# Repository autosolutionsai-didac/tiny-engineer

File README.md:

# Vibe Bot

> Give your AI coding agents a body.

> **Based on [Tiny Engineer](https://github.com/jamro/tiny-engineer) by Krzysztof Jamroz** (github.com/jamro/tiny-engineer). Vibe Bot is an independent fork: XIAO ESP32S3 port, multi-session LED bar, and the `vibebot-hub` session aggregator. It is not an official Tiny Engineer product and is not endorsed by the upstream author. Upstream copyright and licence notices are kept — see [License](#license).

> **Photos:** fork-specific photos and a demo of Vibe Bot are TBD. The upstream preview images in `docs/` depict Tiny Engineer branding and are kept only for attribution history; they are not this product's branding (see [TRADEMARK.md](TRADEMARK.md)). For the original robot in action, see the [upstream Tiny Engineer demo video](https://youtu.be/RX_QRxdXMjg).

Vibe Bot is an open-source, 3D-printable desktop robot that physically acts out what your AI coding agents are doing: reading, thinking, coding, finishing tasks (with an audio cue). It runs on an ESP32 over Wi-Fi and exposes a simple REST API, so any tool that can make an HTTP request can drive it.

**[Build your own](#build-your-own) · [How it works](#how-it-works) · [API](docs/api.md) · [Sessions](docs/sessions.md)**

## Why?

AI coding agents increasingly spend long stretches working on their own. Instead of another spinner or status line, Vibe Bot is a tiny teammate on your desk that visibly reads, thinks, and types while the agents work — and its LED bar shows every running session at a glance.

## How it works

```mermaid
flowchart LR
  Agent[AI agent working] --> Integration[Integration sends events]
  Integration -->|HTTP over Wi-Fi| API[Vibe Bot REST API]
  API --> Robot[Robot moves and reacts]
```

An AI agent works; an integration turns that into events; the robot’s REST API on your LAN receives them; the hardware moves and reacts.

**How it connects**

- **Cursor** — Cursor Agent → Cursor hooks → `vibebot-cursor` script → HTTP over Wi-Fi
- **Antigravity CLI** — Antigravity Agent → lifecycle hooks → `vibebot-antigravity` script → HTTP over Wi-Fi
- **Claude Code** — Claude Code → project hooks → `vibebot-claude-code` script → HTTP over Wi-Fi
- **Bring your own** — Codex or any other agent → your script/plugin/app → HTTP REST

All hit the same Vibe Bot REST API (`/anim`, or `/session` for multi-session state). The ESP32 (Seeed XIAO ESP32S3; legacy ESP32-C3-Zero) runs that API, robot logic, and animations, then drives (and plays audio):

| Hardware | Role |
| --- | --- |
| PCA9685 → 5× servos | Head / neck, hands / body |
| Waveshare 0.91inch OLED (SSD1306) | Status, face, info |
| MAX98357A → speaker | Audio |
| 74AHCT1G125 → 9× WS2812B (XIAO build) | Lamp LED + 8-LED session bar |

Cursor is one example client, not the architecture. Details: [Cursor hooks](docs/hooks.md) · [any integration](docs/integration.md) · [HTTP API](docs/api.md)

## Build your own

**Start here:** [docs/getting-started.md](docs/getting-started.md) — thin checklist (shop → print → wire → flash → assemble → wizard → prove → agent).

New to hardware? Optional skim of **[From Code to Circuits](docs/hardware-for-software-engineers/README.md)** — then return to the checklist.

## Hardware overview

Major pieces (exact models and counts in the BOM):

| Role | Part | Qty |
| --- | --- | --- |
| Main Controller | [Seeed Studio XIAO ESP32S3](https://www.seeedstudio.com/XIAO-ESP32S3-p-5627.html) (legacy build: [Waveshare ESP32-C3-Zero](https://www.waveshare.com/esp32-c3-zero.htm), `pio run -e esp32-c3-devkitm-1`) | 1 |
| Servo Controller PWM | [Adafruit PCA9685](https://www.adafruit.com/product/815) | 1 |
| Actuators | Analog micro servos — **Tower Pro SG90 recommended**; Feetech FS0307 for a compact build; Parametrically designed for any standard micro servos | 5 |
| Display | [Waveshare 0.91inch OLED Module](https://www.waveshare.com/0.91inch-oled-module.htm) (SSD1306, 128×32, I2C) | 1 |
| Audio | [MAX98357A](https://www.adafruit.com/product/3006) + [8 Ω / 1 W speaker](https://www.adafruit.com/product/3923) | 1 + 1 |
| LEDs | 9× WS2812B (1 lamp + 8-LED session bar) via a 74AHCT1G125 level shifter, 330 Ω series resistor | 9 |
| USB / power | Dedicated USB-C power input ([Adafruit 5993 USB-C breakout](https://www.adafruit.com/product/5993) or equivalent), **5 V / 3 A** supply, SS14 Schottky into the XIAO 5V pin, 470 µF bulk capacitor | 1 |
| Structure | 3D-printed parts | — |

Complete inventory and limits: [docs/hardware/components.md](docs/hardware/components.md). What to buy (cart + which servo): [docs/shopping.md](docs/shopping.md).

## Quick start

Firmware is Arduino on [PlatformIO](https://platformio.org/). From the project root:

```bash
pio run                 # build
pio run -t upload       # flash firmware + LittleFS
pio device monitor      # serial (115200)
```

If servos move but audio is silent, run `pio run -t uploadfs` once.

**Wi-Fi (first boot):** join `VibeBot-XXXX`, open `http://192.168.4.1/config`. Wizard: servos, screen orientation, RGB LED, speaker, then a **2.4 GHz** network. OLED shows the join-AP steps.

**Web UI:** `http://vibebot.local/` (or the IP on the OLED) — settings, hardware tests, animations.

**Make it move:**

```bash
curl -X POST "http://vibebot.local/anim?name=ring"
```

Full route list: [docs/api.md](docs/api.md). Settings: [docs/settings.md](docs/settings.md).

## AI integrations

Anything that can `POST` over HTTP can drive the robot:

```bash
curl -X POST "http://vibebot.local/anim?name=typing"
```

Useful `name` values: `typing`, `reading`, `thinking`, `ring`, `welcome`, `wakeup`, `sleep`, `attention`, `error`, `abort`, `dead`, `none`.

**Several agents at once:** report each session with `POST /session?id=…&state=idle|working|waiting|error|ended[&activity=typing|reading|thinking][&agent=…][&label=…]` (list: `GET /sessions`, reset: `POST /sessions/clear`). The robot picks one animation by priority and shows every session on the LED bar. Sessions come from the `vibebot-hub` REST pusher or an AgentDeck daemon on the LAN (`agentdeck` setting, default on) — [docs/sessions.md](docs/sessions.md).

Cursor projects can map agent events to poses via hooks — [docs/hooks.md](docs/hooks.md). Broader patterns and examples: [docs/integration.md](docs/integration.md). Optional extra: sleep/wake when you lock or unlock a Mac — [docs/macos-lock-unlock.md](docs/macos-lock-unlock.md).

## Documentation

| Goal | Doc |
| --- | --- |
| Build end-to-end | [docs/getting-started.md](docs/getting-started.md) |
| Flash firmware | [docs/flash.md](docs/flash.md) |
| Parts / cart | [docs/shopping.md](docs/shopping.md) |
| Wiring / power | [docs/hardware/README.md](docs/hardware/README.md) |
| Printable parts | [3d_models/README.md](3d_models/README.md) |
| Assemble printed parts | [docs/3d/assembly.md](docs/3d/assembly.md) |
| Resize CAD for another servo | [docs/3d/parametric-design.md](docs/3d/parametric-design.md) |
| Servo axes / safe ranges | [docs/robot-movement.md](docs/robot-movement.md) |
| HTTP API | [docs/api.md](docs/api.md) |
| Settings | [docs/settings.md](docs/settings.md) |
| Cursor hooks | [docs/hooks.md](docs/hooks.md) |
| Any IDE / REST | [docs/integration.md](docs/integration.md) |
| Firmware / package tests | [docs/testing.md](docs/testing.md) |
| Full index | [docs/README.md](docs/README.md) |

## Build one, break one, share it

Print it, wire it, change the CAD, swap animations, or hook up a different agent. Issues and PRs welcome — especially new integrations. See [CONTRIBUTING.md](CONTRIBUTING.md). Vulnerabilities: [SECURITY.md](SECURITY.md). Conduct: [CODE_OF_CONDUCT.md](CODE_OF_CONDUCT.md).

## License

- **Software** (firmware, integrations, scripts, documentation) — [MIT](LICENSE)
- **Hardware designs** (CAD source and `.3mf` printables in [`3d_models/`](3d_models/); KiCad PCBs in [`hardware/`](hardware/)) — [CERN-OHL-S-2.0](3d_models/LICENSE)

Copyright (c) 2026 Krzysztof Jamroz and contributors. Vibe Bot is based on the Tiny Engineer open hardware design by Krzysztof Jamroz; the upstream Source Location for the CERN-OHL-S designs remains `https://github.com/jamro/tiny-engineer` (see [3d_models/NOTICE](3d_models/NOTICE) and [hardware/NOTICE](hardware/NOTICE)).

See [LICENSING.md](LICENSING.md) for scope and effective date. The **Tiny Engineer** name, logo, AI emblem, and branded project images are not licensed and are not used as this fork's branding — see [TRADEMARK.md](TRADEMARK.md).

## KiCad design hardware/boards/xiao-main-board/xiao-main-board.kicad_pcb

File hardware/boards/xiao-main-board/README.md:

# xiao-main-board

Carrier PCB for the Seeed XIAO ESP32S3 build: hand-solderable sockets for the existing modules, a 5 V / 3 A power input, a buffered WS2812 output, and small aux headers. Same idea as [`main-control-board`](../main-control-board/) (sockets, not integrated chips), sized for the robot base.

- **Status:** draft, not manufactured (rev v0.1, 2026-10-18). Schematic and fully routed layout, KiCad review only.
- **KiCad:** 10 (checked with kicad-cli 10.0.7)
- **Board:** 70.0 × 45.0 mm, 2 layers, FR4 1.6 mm, 1 oz. GND pour on both layers with stitching vias. 4 × M2 mounting holes (2.2 mm NPTH) at (10.7, 3.0), (59.3, 3.0), (10.7, 35.4) and (59.3, 35.4) mm from the top-left corner. The two lower holes sit under the XIAO and the MAX98357A modules, so screw the board down before plugging those in.
- **Interfaces:** XIAO ESP32S3 (2 × 1×7 sockets), Adafruit PCA9685 #815 (2 × 1×6 sockets), MAX98357A breakout (1×7 socket), SSD1306 OLED (1×4 header), Adafruit 5993 USB-C breakout (1×4 socket, power only), 2-pin screw terminal, WS2812 JST-PH 3-pin, touch 1×2 header, UART 1×3 header.
- **Built:** not manufactured. **Tested:** not tested.
- **ERC / DRC:** `python3 scripts/check_pcb.py` passes: ERC 0 errors, DRC 0 errors / 0 unconnected / 0 schematic-parity issues, and the netlist matches `expected-nets.yml`. The remaining warnings are listed under [Known warnings](#known-warnings).

Pin plan and firmware mapping: [`include/pins.h`](../../../include/pins.h) and [`docs/hardware/pinout.md`](../../../docs/hardware/pinout.md). Contribution rules: [`docs/pcb.md`](../../../docs/pcb.md).

## XIAO ESP32S3 pinout used

The XIAO plugs in with its USB-C facing the left board edge. The receptacle overhangs the board by about 1.5 mm, and the overhang is marked on silkscreen and courtyard.

| XIAO | GPIO | Net | Goes to |
| --- | --- | --- | --- |
| D0 | 1 | `LED_DIN_3V3` | U2 74AHCT1G125 input A |
| D1 | 2 | `TOUCH_D1` | J8.1 (reserved: touch pad or button) |
| D2 | 3 | open | S3 strapping pin, left unused |
| D3 | 4 | `PCA_OE` | J1.5 / J2.5 PCA9685 OE (active low) |
| D4 | 5 | `I2C_SDA` | PCA9685, OLED, optional R2 |
| D5 | 6 | `I2C_SCL` | PCA9685, OLED, optional R3 |
| D6 | 43 | `UART_TX` | J9.1 |
| D7 | 44 | `UART_RX` | J9.2 |
| D8 | 7 | `I2S_BCLK` | J3.2 MAX98357A BCLK |
| D9 | 8 | `I2S_LRC` | J3.1 MAX98357A LRC |
| D10 | 9 | `I2S_DIN` | J3.3 MAX98357A DIN |
| 5V | – | `+5V_XIAO` | D1 SS14 cathode |
| 3V3 | – | `+3V3` | PCA9685 VCC, OLED VCC, R2/R3 |
| GND | – | `GND` | |

Source for the pin numbers: Seeed's own KiCad library ([Seeed-Studio/OPL_Kicad_Library](https://github.com/Seeed-Studio/OPL_Kicad_Library), commit `b0035c5`, "Seeed Studio XIAO Series Library": symbol `XIAO-ESP32-S3-SMD` and footprint `XIAO-ESP32-S3-DIP`). Pins 1–7 are D0–D6 down the left side with USB at the top. Pins 8–14 are D7, D8, D9, D10, 3V3, GND and 5V going up the right side. That matches the Seeed wiki pinout (left side D0…D6, right side 5V, GND, 3V3, D10, D9, D8, D7 from top to bottom). The project symbol and footprint (`libraries/`, nickname `XiaoMainBoard`) were redrawn from those dimensions: 21 × 17.8 mm module, 2.54 mm pitch, rows 15.24 mm apart.

## Power

```
J5 (5993 VBUS) ─┐
J6 (terminal +)─┴─ +5V rail ─┬─ C1 470 µF + C2 100 nF
                             ├─ J1.1 / J2.1  PCA9685 V+ (servos)   ← 1.5 mm back-layer trunk
                             ├─ J3.7 MAX98357A VIN
                             ├─ J7.1 LED chain + U2 VCC (C3 100 nF)
                             └─ D1 SS14 ──► +5V_XIAO ── XIAO 5V pin
```

- **SS14 orientation** (confirmed in the `kicad-cli sch export netlist` output): **anode `D1.2:A` on `+5V`** (the rail) and **cathode `D1.1:K` on `+5V_XIAO`**, which is the XIAO 5V pin `U1.14`. The rail can feed the XIAO, but a USB host plugged into the XIAO cannot back-feed the servo rail. The SMA cathode band is pad 1, toward the left (XIAO) side. The silkscreen shows the band.
- Use a single **5 V / 3 A** supply on J5 (Adafruit 5993) **or** J6 (screw terminal), not both at once. The XIAO's own USB-C is for flashing and serial only. Do not power the servos from it.
- PCA9685 **VCC** = `+3V3` (logic) and **V+** = `+5V` (servo rail). They are separate nets. Do not bridge them.
- When the XIAO USB and the rail are both live, the XIAO 5V pin sees about rail − 0.35 V through D1 and the host's VBUS in parallel. A rail above about 5.3 V could make the rail the supply that wins (see [review items](#needs-human-review-before-ordering)).
- Net classes in `xiao-main-board.kicad_pro`, with matching rules in `xiao-main-board.kicad_dru`:

  | Class | Nets | Default width | DRU minimum |
  | --- | --- | --- | --- |
  | `Power5V` | `+5V` | 1.2 mm | 1.0 mm |
  | `Power5VXiao` | `+5V_XIAO` | 0.6 mm | 0.5 mm |
  | `Power3V3` | `+3V3` | 0.4 mm | 0.4 mm |
  | `GND` | `GND` | 0.4 mm | 0.4 mm |
  | `Default` | signals | 0.25 mm | – |

  The servo trunk from J6 through C1 to both PCA9685 V+ pins is 1.5 mm on the back layer.

## Connector pinouts

| Ref | Part | Pin 1 → n |
| --- | --- | --- |
| U1 | XIAO ESP32S3 on 2 × 1×7 sockets | see table above |
| J1, J2 | PCA9685 #815 sockets, 58.42 mm apart | 1 V+ (`+5V`), 2 VCC (`+3V3`), 3 SDA, 4 SCL, 5 OE (`PCA_OE`), 6 GND. Same order as main-control-board; V+ is the lower pin. |
| J3 | MAX98357A 1×7 socket | 1 LRC, 2 BCLK, 3 DIN, 4 GAIN (open), 5 SD (open), 6 GND, 7 VIN (`+5V`) |
| J4 | OLED 1×4 male header | 1 VCC (`+3V3`), 2 GND, 3 SDA, 4 SCL. Same order as main-control-board J2. |
| J5 | Adafruit 5993 1×4 socket | 1 D+ (open), 2 D− (open), 3 VBUS (`+5V`), 4 GND. Same order as main-control-board J7; data is not used. |
| J6 | Screw terminal, 3.5 mm pitch | 1 `+5V`, 2 GND. The wire entry faces the bottom edge. |
| J7 | JST-PH 3-pin (B3B-PH-K) | 1 `+5V`, 2 DATA (`LED_DATA`, after 330 Ω), 3 GND. Chain: index 0 lamp LED, then the 8-LED session bar. |
| J8 | 1×2 header | 1 `TOUCH_D1` (XIAO D1), 2 GND |
| J9 | 1×3 header | 1 TX (D6), 2 RX (D7), 3 GND. These are XIAO-side names: connect the adapter's RX to pin 1. |

## BOM

| Qty | Ref | Value / part | Footprint | Example part number |
| --- | --- | --- | --- | --- |
| 1 | U1 | Seeed Studio XIAO ESP32S3 (U.FL antenna included) | `XiaoMainBoard:Seeed_XIAO_ESP32S3_Socketed` | Seeed 113991114 |
| 2 | (U1) | 1×7 female header, 2.54 mm, 8.5 mm tall | (part of the U1 footprint) | Würth 61300711821 |
| 1 | U2 | 74AHCT1G125, SOT-23-5 | `Package_TO_SOT_SMD:SOT-23-5` | TI SN74AHCT1G125DBVR |
| 1 | D1 | SS14 Schottky, 1 A 40 V | `Diode_SMD:D_SMA` | SS14 (onsemi / MCC) |
| 1 | C1 | 470 µF 10 V electrolytic, 8 × 11.5 mm | `Capacitor_THT:CP_Radial_D8.0mm_P3.50mm` | Panasonic EEU-FR1A471 |
| 2 | C2, C3 | 100 nF X7R 25 V | `Capacitor_SMD:C_0805_2012Metric` | Yageo CC0805KRX7R9BB104 |
| 1 | R1 | 330 Ω 1 % | `Resistor_SMD:R_0805_2012Metric` | Yageo RC0805FR-07330RL |
| 2 | R2, R3 | 4.7 kΩ 1 %, **DNP** | `Resistor_SMD:R_0805_2012Metric` | Yageo RC0805FR-074K7L |
| 2 | J1, J2 | 1×6 female header, 2.54 mm | `Connector_PinSocket_2.54mm:PinSocket_1x06_P2.54mm_Vertical` | Würth 61300611821 |
| 1 | J3 | 1×7 female header, 2.54 mm | `…PinSocket_1x07_P2.54mm_Vertical` | Würth 61300711821 |
| 1 | J5 | 1×4 female header, 2.54 mm | `…PinSocket_1x04_P2.54mm_Vertical` | Würth 61300411821 |
| 1 | J4 | 1×4 male header | `Connector_PinHeader_2.54mm:PinHeader_1x04_P2.54mm_Vertical` | Würth 61300411121 |
| 1 | J9 | 1×3 male header | `…PinHeader_1x03_P2.54mm_Vertical` | Würth 61300311121 |
| 1 | J8 | 1×2 male header | `…PinHeader_1x02_P2.54mm_Vertical` | Würth 61300211121 |
| 1 | J6 | 2-pin screw terminal, 3.5 mm | `TerminalBlock_Phoenix:TerminalBlock_Phoenix_PT-1,5-2-3.5-H_1x02_P3.50mm_Horizontal` | Phoenix Contact 1984617 |
| 1 | J7 | JST-PH 3-pin vertical (mates PHR-3) | `Connector_JST:JST_PH_B3B-PH-K_1x03_P2.00mm_Vertical` | JST B3B-PH-K-S |
| 4 | H1–H4 | M2 screws + standoffs (no part on the board) | `MountingHole:MountingHole_2.2mm_M2` | – |
| – | modules | PCA9685 (Adafruit 815), MAX98357A breakout, SSD1306 0.91" OLED, Adafruit 5993, WS2812B × 9 | plug in | see [`docs/hardware/components.md`](../../../docs/hardware/components.md) |

All stock symbols and footprints come from the KiCad 10 libraries. They are also embedded in the `.kicad_sch` / `.kicad_pcb` files, so the project opens without the global libraries. The only custom parts are the XIAO symbol and footprint in `libraries/`.

## Assembly order

1. SMD parts: U2 (check the pin-1 dot), R1, C2, C3, D1 (cathode band toward the XIAO / left). R2/R3 are DNP.
2. Low THT parts: the J9/J8/J4 headers, J7 JST, J6 terminal.
3. Sockets: XIAO 2 × 1×7, J1/J2 1×6, J3 1×7, J5 1×4. Seat each one square, for example with the module plugged in while you solder.
4. C1 470 µF last. Watch polarity: `+` is the square pad, next to the XIAO.
5. Screw the board down (4 × M2) **before** you plug in the XIAO and the MAX98357A. Two holes are under them.
6. Before plugging in any module: apply 5 V on J6 with a current-limited bench supply. Check `+5V` on J1.1, J2.1, J3.7 and J7.1, about 4.6–4.7 V on the XIAO 5V socket pin, and no short to GND.
7. Plug in the modules. The PCA9685 sits over the SMD area between J1 and J2, about 11 mm up, with its servo header strip toward the top board edge. The MAX98357A sits over U2/R1/C3. The Adafruit 5993 overhangs the bottom edge.

## Bench safety

- Use a **5 V / 3 A** supply on J5 or J6 only. Never power the servos from the XIAO USB-C or from its 3.3 V regulator.
- Keep the XIAO U.FL antenna and its FPC/rod antenna clear of metal, the servo wiring and dense plastic. Route it away from the PCA9685 and servo rail.
- MAX98357A outputs are bridge-tied: **SPK− is not ground.**

## Known warnings

`check_pcb.py` gates only on errors. With `--severity-all` these warnings remain:

- `lib_symbol_issues` / `footprint_link_issues` / `lib_footprint_issues`: the CI and dev container has no stock KiCad libraries installed. The parts are embedded in the files, and these warnings go away on a normal KiCad install.
- `silk_edge_clearance` (4): intentional. The silkscreen marks the XIAO USB-C overhang and the J6 terminal body, which reach the board edge.
- Pad J5.4 (GND) uses a solid zone connection. The back-layer pour around it is an island between signal tracks, which DRC reports as a starved thermal relief. It is connected through the front pour.

## Needs human review before ordering

- Check the PCA9685 #815 header spacing (58.42 mm assumed, same as main-control-board) and which long edge the servo headers are on. Check the generic MAX98357A breakout size (about 18 × 19 mm assumed, overhanging U2/R1/C3) and the Adafruit 5993 header order and orientation (copied from main-control-board J7).
- OLED pin order: J4 is VCC, GND, SDA, SCL. Many 0.91" modules are GND, VCC, SCL, SDA, so check yours or use a crossed cable.
- The XIAO USB-C and the external 5 V should not both be live with a rail above about 5.3 V (see Power).
- Layout was autorouted (Freerouting) and then cleaned up: GND stitching, +5V neck-downs widened to the 1 mm rule, a locked 1.5 mm servo trunk. Review the GND return path for servo current in region B. Most of it flows on the front pour because the back +5V trunk splits the back pour.
- Check that the mounting holes line up with the enclosure ("under the desk" base), and check the stack-up heights: modules sit about 11 mm above the PCB on 8.5 mm sockets, and C1 is 11.5 mm tall.
- Run the GUI DRC once with the stock libraries installed (footprint/library mismatch check).

## Files

- `xiao-main-board.kicad_pro` / `.kicad_sch` / `.kicad_pcb` / `.kicad_dru`, `sym-lib-table`, `fp-lib-table`
- `libraries/symbols/xiao_main_board.kicad_sym`, `libraries/footprints/xiao_main_board.pretty/`
- `expected-nets.yml`: every named net (critical net list for review)
- `xiao-main-board-render-top.png`, `xiao-main-board-render-bottom.png`: `kicad-cli pcb render` output

## License

CERN-OHL-S-2.0. See [`hardware/LICENSE`](../../LICENSE) and [`hardware/NOTICE`](../../NOTICE). This board is part of Vibe Bot, a fork of Tiny Engineer by Krzysztof Jamroz.

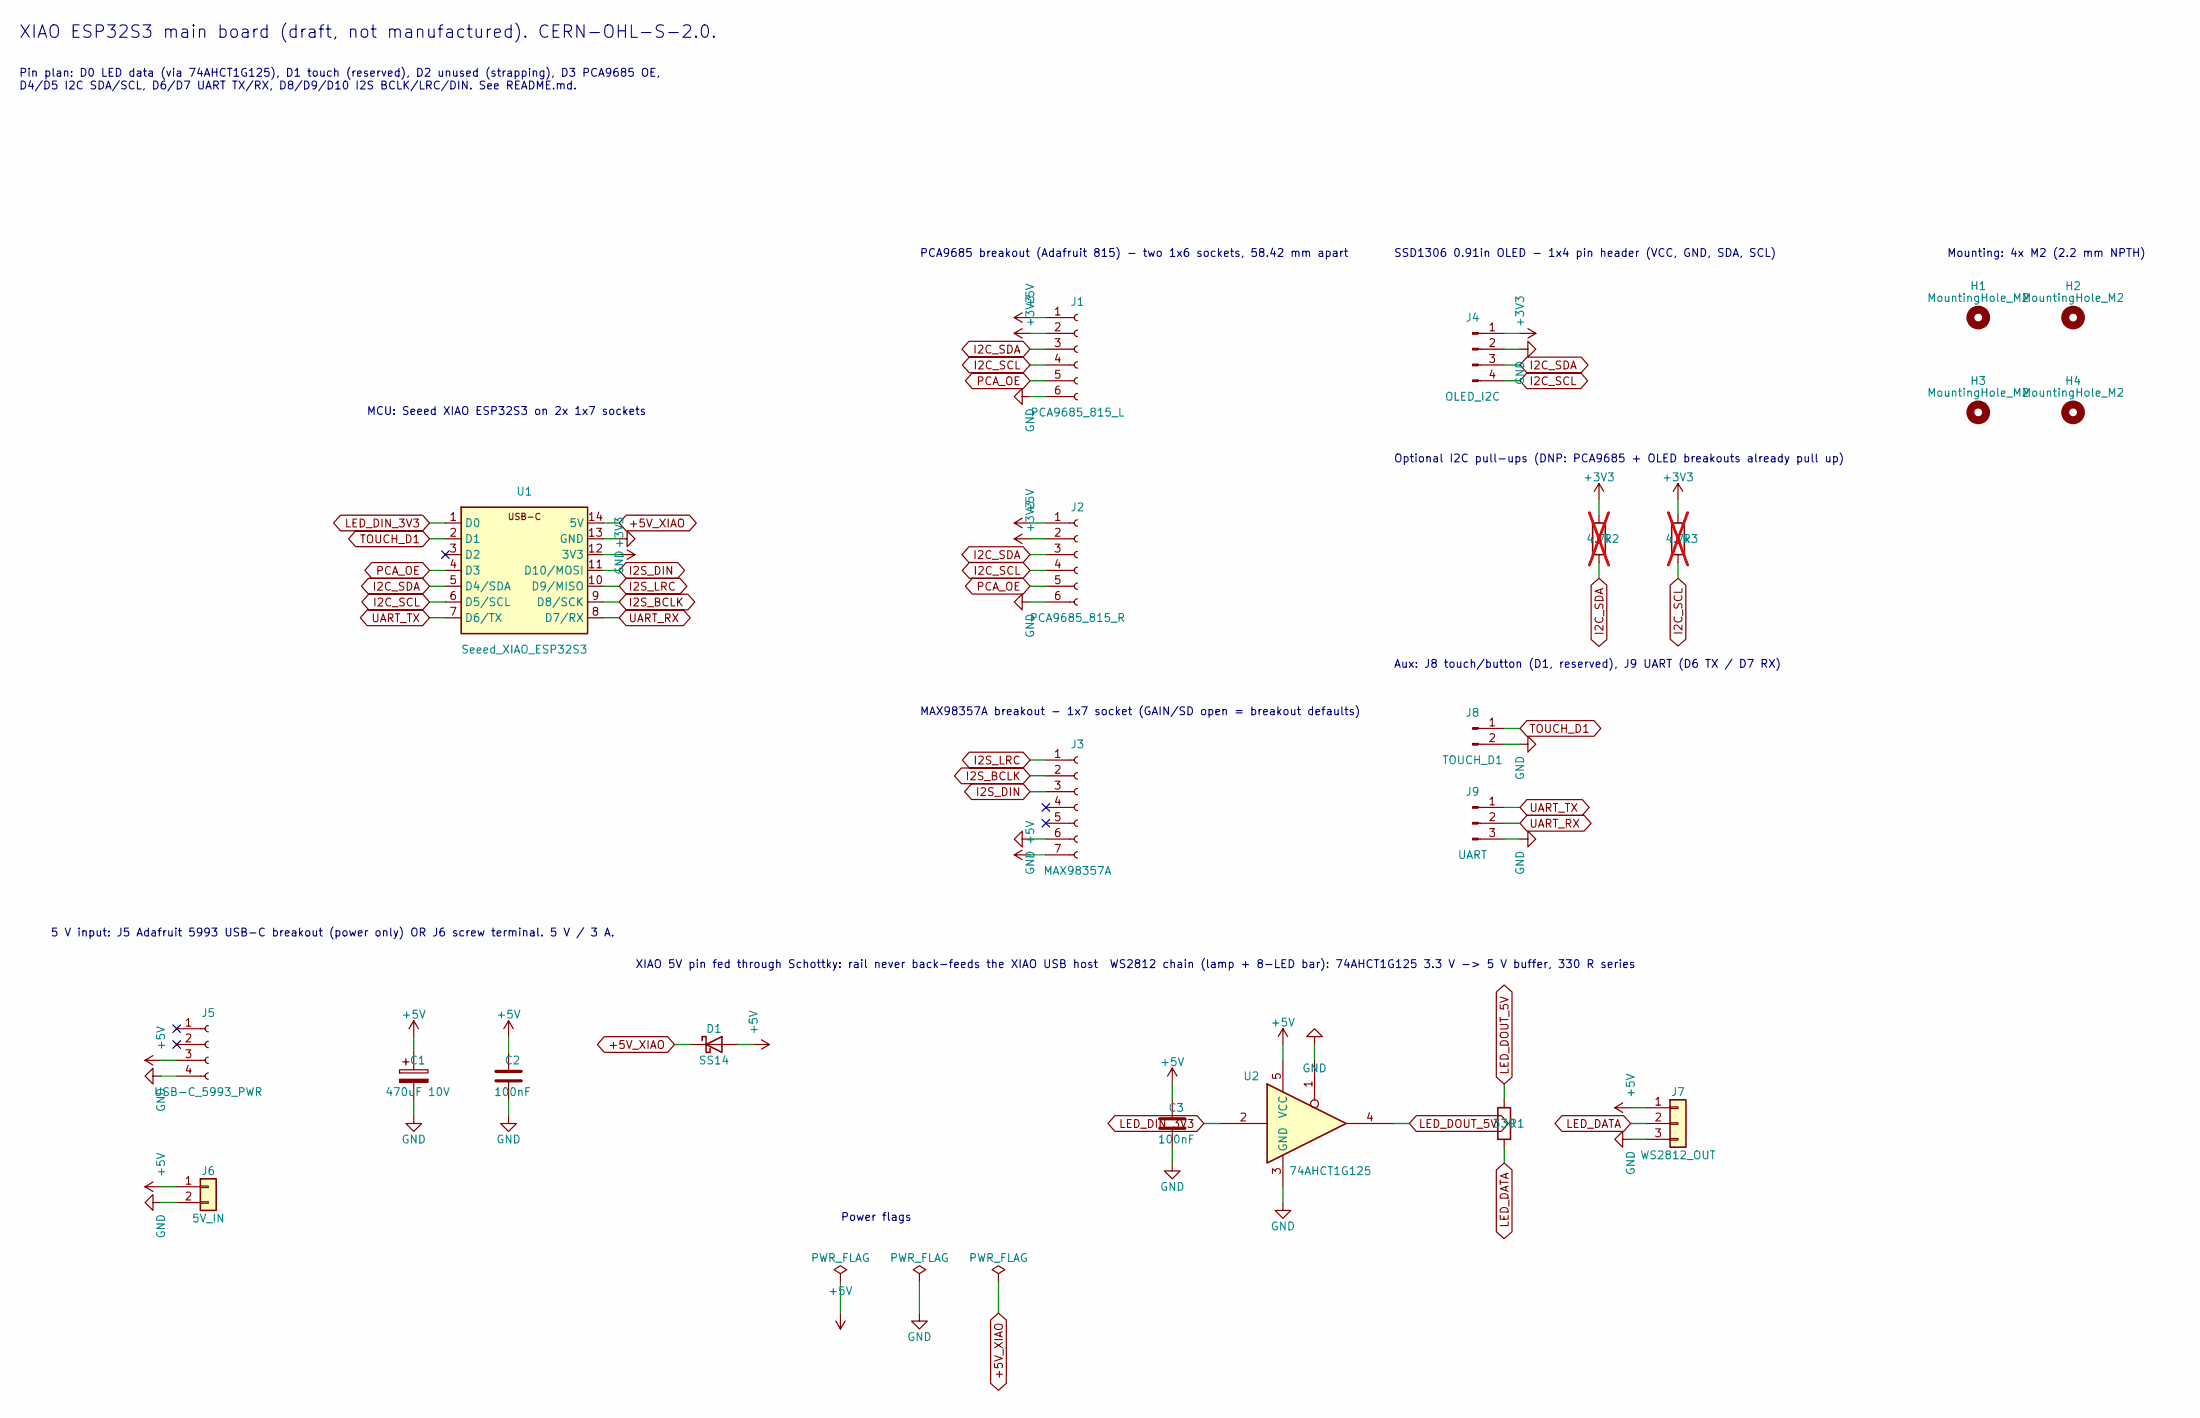
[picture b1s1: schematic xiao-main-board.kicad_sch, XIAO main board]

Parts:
C1: 470uF 10V; CP_Radial_D8.0mm_P3.50mm; MPN Panasonic EEU-FR1A471 (470 uF 10 V, 8x1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
C2, C3: 100nF; C_0805_2012Metric; MPN 100 nF 0805 X7R 25 V
D1: SS14; D_SMA; MPN SS14 (1 A 40 V Schottky, SMA)
H1, H2, H3, H4: MountingHole_M2; MountingHole_2.2mm_M2; MPN M2 screw + standoff
J1: PCA9685_815_L; PinSocket_1x06_P2.54mm_Vertical; MPN 1x6 female header 2.54 mm, 8.5 mm (e.g.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
J2: PCA9685_815_R; PinSocket_1x06_P2.54mm_Vertical; MPN 1x6 female header 2.54 mm, 8.5 mm (e.g.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
J3: MAX98357A; PinSocket_1x07_P2.54mm_Vertical; MPN 1x7 female header 2.54 mm, 8.5 mm (e.g.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
J4: OLED_I2C; PinHeader_1x04_P2.54mm_Vertical; MPN 1x4 male header 2.54 mm (e.g. Wurth 613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
J5: USB-C_5993_PWR; PinSocket_1x04_P2.54mm_Vertical; MPN 1x4 female header 2.54 mm (e.g. Wurth 6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
J6: 5V_IN; TerminalBlock_Phoenix_PT-1,5-2-3.5-H_1x02_P3.50mm_Horizontal; MPN Phoenix Contact PT 1,5/ 2-3,5-H (198461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
J7: WS2812_OUT; JST_PH_B3B-PH-K_1x03_P2.00mm_Vertical; MPN JST B3B-PH-K-S (mates PHR-3)
J8: TOUCH_D1; PinHeader_1x02_P2.54mm_Vertical; MPN 1x2 male header 2.54 mm
J9: UART; PinHeader_1x03_P2.54mm_Vertical; MPN 1x3 male header 2.54 mm
R1: 330; R_0805_2012Metric; MPN 330 Ohm 0805 1%
R2, R3: 4.7k; R_0805_2012Metric; MPN 4.7 kOhm 0805 1% (DNP); not fitted
U1: Seeed_XIAO_ESP32S3; Seeed_XIAO_ESP32S3_Socketed; MPN Seeed 113991114 (XIAO ESP32S3)
U2: 74AHCT1G125; SOT-23-5; MPN TI SN74AHCT1G125DBVR

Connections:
+3V3: J1.2, J2.2, J4.1, R2.1, R3.1, U1.12 (3V3)
+5V: C1.1, C2.1, C3.1, D1.2 (A), J1.1, J2.1, J3.7, J5.3, J6.1, J7.1, U2.5 (VCC)
+5V_XIAO: D1.1 (K), U1.14 (5V)
GND: C1.2, C2.2, C3.2, J1.6, J2.6, J3.6, J4.2, J5.4, J6.2, J7.3, J8.2, J9.3, U1.13 (GND), U2.1, U2.3 (GND)
I2C_SCL: J1.4, J2.4, J4.4, R3.2, U1.6 (D5/SCL)
I2C_SDA: J1.3, J2.3, J4.3, R2.2, U1.5 (D4/SDA)
I2S_BCLK: J3.2, U1.9 (D8/SCK)
I2S_DIN: J3.3, U1.11 (D10/MOSI)
I2S_LRC: J3.1, U1.10 (D9/MISO)
LED_DATA: J7.2, R1.2
LED_DIN_3V3: U1.1 (D0), U2.2
LED_DOUT_5V: R1.1, U2.4
PCA_OE: J1.5, J2.5, U1.4 (D3)
TOUCH_D1: J8.1, U1.2 (D1)
UART_RX: J9.2, U1.8 (D7/RX)
UART_TX: J9.1, U1.7 (D6/TX)

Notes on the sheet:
PCA9685 breakout (Adafruit 815) - two 1x6 sockets, 58.42 mm apart
Aux: J8 touch/button (D1, reserved), J9 UART (D6 TX / D7 RX)
MAX98357A breakout - 1x7 socket (GAIN/SD open = breakout defaults)
MCU: Seeed XIAO ESP32S3 on 2x 1x7 sockets
Mounting: 4x M2 (2.2 mm NPTH)
XIAO ESP32S3 main board (draft, not manufactured). CERN-OHL-S-2.0.
Optional I2C pull-ups (DNP: PCA9685 + OLED breakouts already pull up)
SSD1306 0.91in OLED - 1x4 pin header (VCC, GND, SDA, SCL)
5 V input: J5 Adafruit 5993 USB-C breakout (power only) OR J6 screw terminal. 5 V / 3 A.
WS2812 chain (lamp + 8-LED bar): 74AHCT1G125 3.3 V -> 5 V buffer, 330 R series
Power flags
Pin plan: D0 LED data (via 74AHCT1G125), D1 touch (reserved), D2 unused (strapping), D3 PCA9685 OE, D4/D5 I2C SDA/SCL, D6/D7 UART TX/RX, D8/D9/D10 I2S BCLK/LRC/DIN. See README.md.
XIAO 5V pin fed through Schottky: rail never back-feeds the XIAO USB host

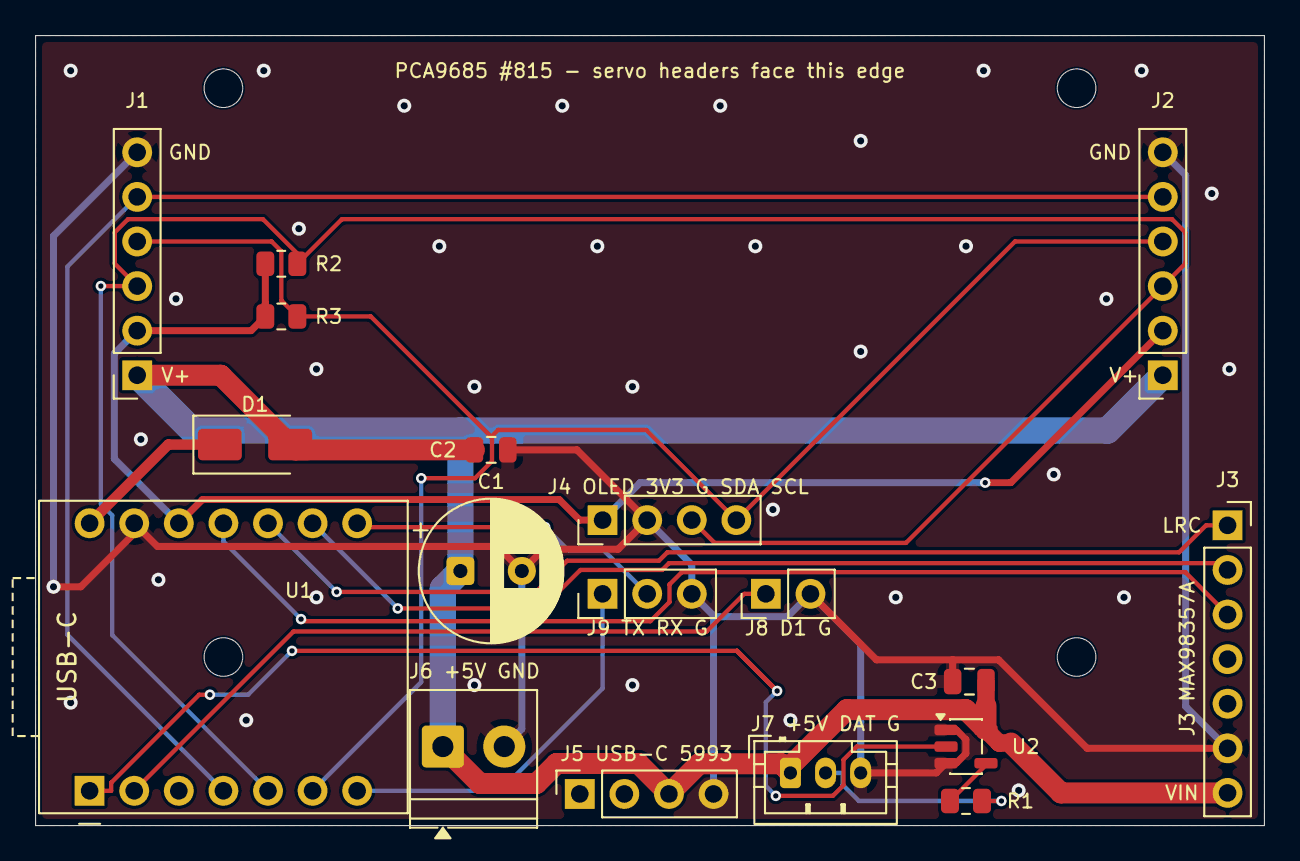
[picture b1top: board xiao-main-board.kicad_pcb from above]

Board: 2 copper layers, 70.0 x 45.0 mm, 22 parts (0 on the bottom side), 16 nets.

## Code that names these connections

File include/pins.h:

#pragma once

#include <cstdint>

// =====================================================
// PINOUT
// =====================================================
//
// Board-conditional pin maps. Keep docs/hardware/pinout.md in sync.
//   CONFIG_IDF_TARGET_ESP32S3 -> Seeed Studio XIAO ESP32S3 (default target)
//   otherwise                 -> Waveshare ESP32-C3-Zero (legacy target)

#if __has_include(<sdkconfig.h>)
#include <sdkconfig.h>
#endif

#if defined(CONFIG_IDF_TARGET_ESP32S3)

constexpr const char* BOARD_NAME = "XIAO ESP32S3";

// I2C -> PCA9685 (0x40) + OLED (0x3C)
constexpr int I2C_SDA = 5;   // D4
constexpr int I2C_SCL = 6;   // D5

// I2S -> MAX98357A
constexpr int I2S_BCLK = 7;  // D8
constexpr int I2S_LRC  = 8;  // D9
constexpr int I2S_DIN  = 9;  // D10

// WS2812B chain via 74AHCT1G125 level shifter: index 0 = lamp, 1..8 = session bar
constexpr int RGB_LED_PIN = 1;  // D0
constexpr int LED_CHAIN_LENGTH = 9;
constexpr int LED_BAR_FIRST_INDEX = 1;
constexpr int LED_BAR_LENGTH = 8;

// PCA9685 output enable (active LOW), wired on the XIAO board: D3 / GPIO4.
// Boot drives it HIGH (outputs off) until PWM positions are loaded, then LOW.
constexpr bool PCA9685_OE_WIRED = true;
constexpr int PCA9685_OE_PIN = 4;  // D3

// Reserved / free: D1 GPIO2 (future touch/button), D2 GPIO3 (strapping, keep
// unused), D6 GPIO43 UART TX, D7 GPIO44 UART RX.

#else  // legacy ESP32-C3-Zero

constexpr const char* BOARD_NAME = "ESP32-C3-Zero";

// I2C -> PCA9685 + OLED
constexpr int I2C_SDA = 0;   // GP0
constexpr int I2C_SCL = 1;   // GP1

// I2S -> MAX98357A
constexpr int I2S_BCLK = 2;  // GP2
constexpr int I2S_LRC  = 3;  // GP3
constexpr int I2S_DIN  = 4;  // GP4

// Built-in WS2812 RGB (the "chain" is just this one LED; no session bar)
constexpr int RGB_LED_PIN = 10;
constexpr int LED_CHAIN_LENGTH = 1;
constexpr int LED_BAR_FIRST_INDEX = 1;
constexpr int LED_BAR_LENGTH = 0;

// PCA9685 output enable (active LOW). GP5 → OE pending; schematic/PCB do not implement that net.
constexpr bool PCA9685_OE_WIRED = false;
constexpr int PCA9685_OE_PIN = 5;

#endif

// =====================================================
// AUDIO
// =====================================================

constexpr int SAMPLE_RATE = 44100;

// =====================================================
// PCA9685 / SERVOS
// =====================================================

constexpr uint8_t PCA9685_ADDRESS = 0x40;

constexpr int SERVO_STEP_MS = 10;

// Boot centering / sleep-pose rate (deg/s)
constexpr float SERVO_BOOT_SPEED_DEG_S = 35.0f;

// Servo pulse range
constexpr int SERVO_MIN_US = 800;
constexpr int SERVO_MAX_US = 2200;

// =====================================================
// OLED
// =====================================================

constexpr int OLED_WIDTH  = 128;
constexpr int OLED_HEIGHT = 32;
constexpr uint8_t OLED_ADDRESS = 0x3C;

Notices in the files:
hardware/boards/xiao-main-board/xiao-main-board.kicad_pcb:
Vibe Bot  CERN-OHL-S-2.0
